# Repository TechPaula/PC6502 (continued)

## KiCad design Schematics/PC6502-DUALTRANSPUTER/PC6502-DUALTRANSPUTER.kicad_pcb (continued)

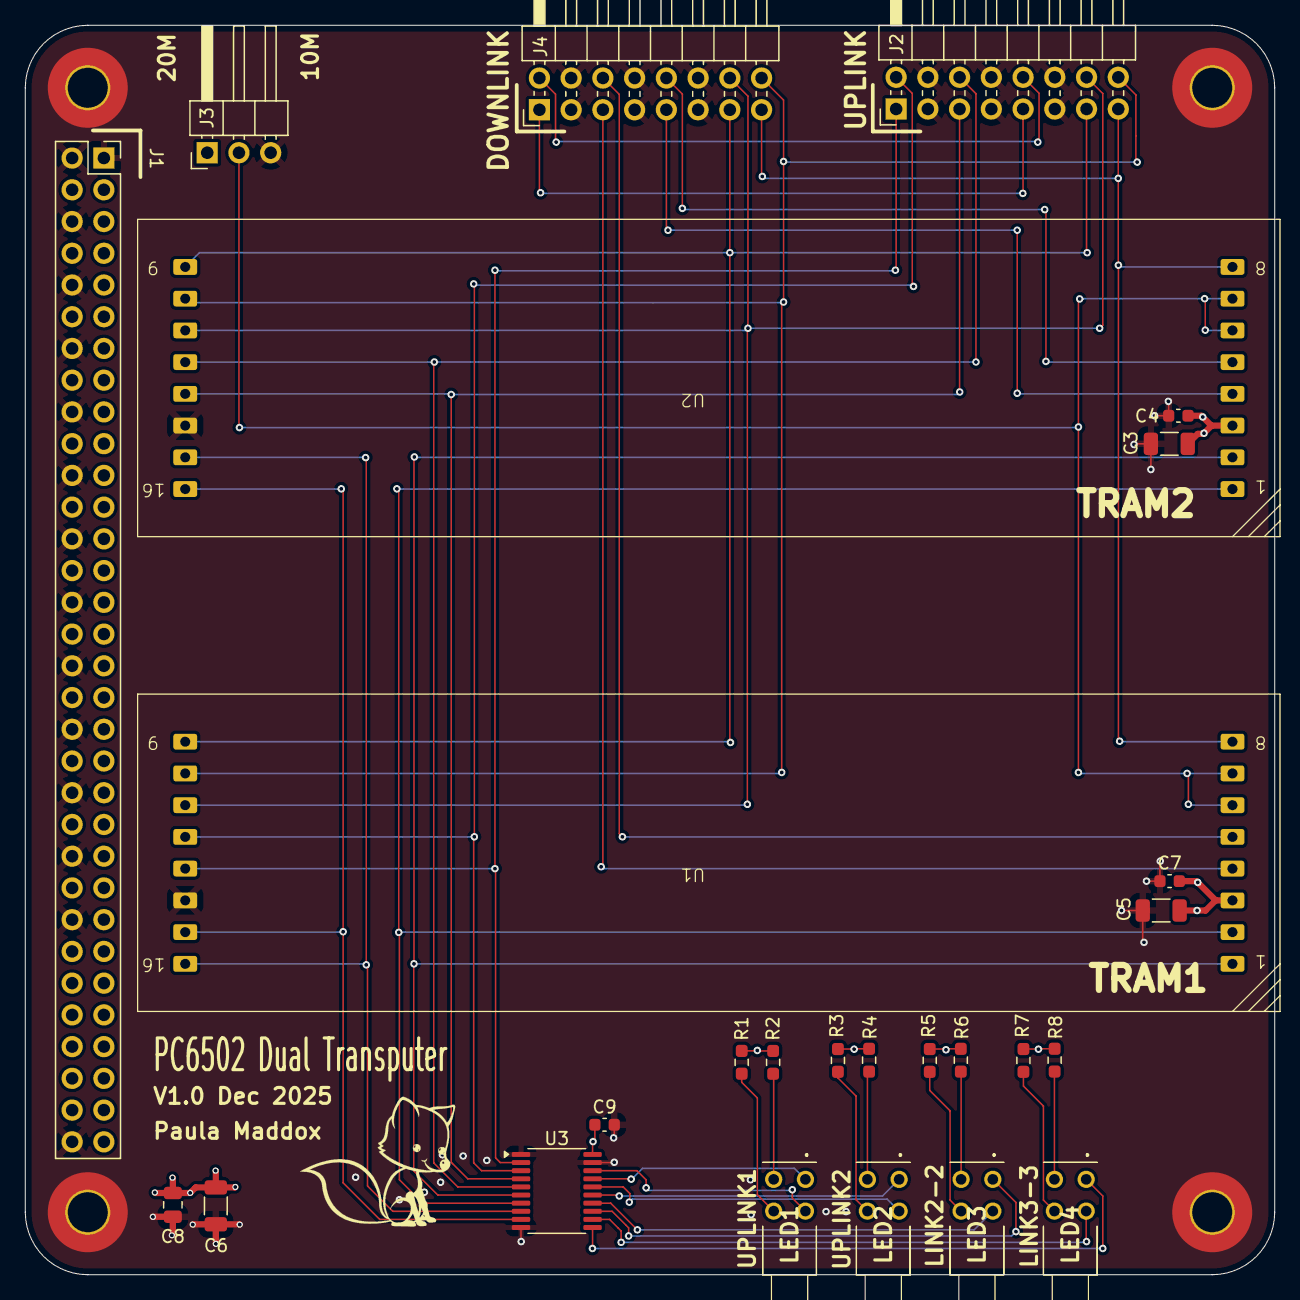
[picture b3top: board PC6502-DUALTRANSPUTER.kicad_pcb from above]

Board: 4 copper layers, 100.0 x 100.0 mm, 31 parts (0 on the bottom side), 37 nets.

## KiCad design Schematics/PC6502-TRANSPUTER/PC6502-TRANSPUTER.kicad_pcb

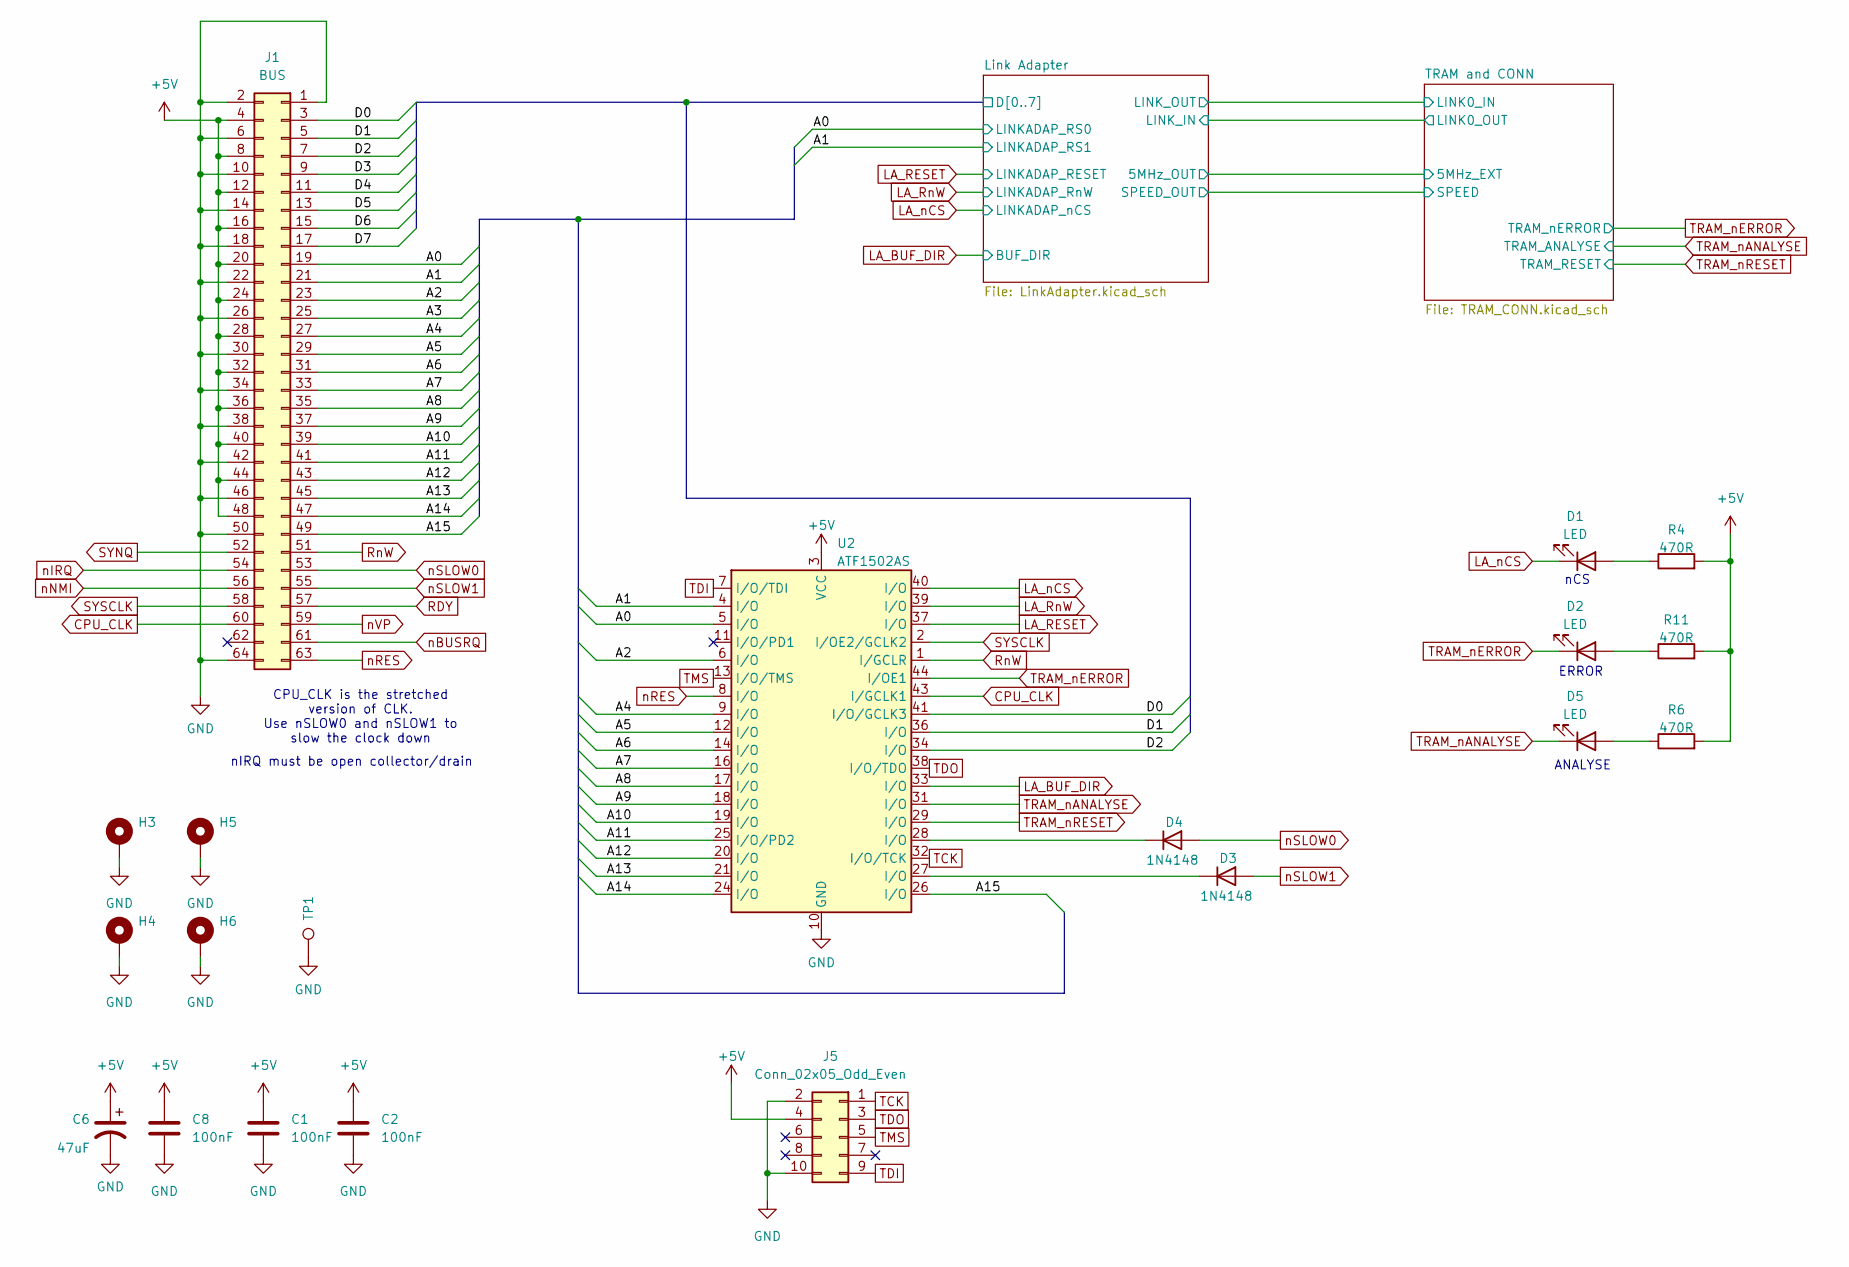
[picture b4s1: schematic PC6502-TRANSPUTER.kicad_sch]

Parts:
C1, C2: 100nF; C_0603_1608Metric
C6: 47uF; C_1206_3216Metric; LCSC C96123
C8: 100nF; C_0805_2012Metric
D1, D2, D5: LED; LTL4221NHBP; LCSC DNF
D3, D4: 1N4148; D_DO-35_SOD27_P7.62mm_Horizontal; LCSC DNF
H3, H4, H5, H6: MountingHole_Pad; MountingHole_3.2mm_M3_Pad_TopBottom; LCSC DNF
J1: BUS; PinSocket_2x32_P2.54mm_Vertical; LCSC DNF
J5: Conn_02x05_Odd_Even; PinHeader_2x05_P2.54mm_Vertical; LCSC DNF
R4, R6, R11: 470R; R_0603_1608Metric_Pad0.98x0.95mm_HandSolder; LCSC C23179
TP1: TestPoint; TestPoint_Loop_D1.80mm_Drill1.0mm_Beaded; LCSC DNF
U2: ATF1502AS; PLCC-44_THT-Socket; LCSC DNF

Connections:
+5V: C1.1, C2.1, C6.1, C8.1, J1.4, J1.8, J1.12, J1.16, J1.20, J1.24, J1.28, J1.32, J1.36, J1.40, J1.44, J1.48, J5.4, R4.2, R6.2, R11.2, U2.3 (VCC), U2.15 (VCC), U2.23 (VCC), U2.35 (VCC); also elsewhere on the board
/A0: J1.19, U2.5 (I/O); also elsewhere on the board
/A1: J1.21, U2.4 (I/O); also elsewhere on the board
/A2: J1.23, U2.6 (I/O)
/A3: J1.25
/A4: J1.27, U2.9 (I/O)
/A5: J1.29, U2.12 (I/O)
/A6: J1.31, U2.14 (I/O)
/A7: J1.33, U2.16 (I/O)
/A8: J1.35, U2.17 (I/O)
/A9: J1.37, U2.18 (I/O)
/A10: J1.39, U2.19 (I/O)
/A11: J1.41, U2.25 (I/O/PD2)
/A12: J1.43, U2.20 (I/O)
/A13: J1.45, U2.21 (I/O)
/A14: J1.47, U2.24 (I/O)
/A15: J1.49, U2.26 (I/O)
/Link Adapter/D0: J1.3, U2.41 (I/O/GCLK3); also elsewhere on the board
/Link Adapter/D1: J1.5, U2.36 (I/O); also elsewhere on the board
/Link Adapter/D2: J1.7, U2.34 (I/O); also elsewhere on the board
/Link Adapter/D3: J1.9; also elsewhere on the board
/Link Adapter/D4: J1.11; also elsewhere on the board
/Link Adapter/D5: J1.13; also elsewhere on the board
/Link Adapter/D6: J1.15; also elsewhere on the board
/Link Adapter/D7: J1.17; also elsewhere on the board
CPU_CLK: J1.60, U2.43 (I/GCLK1)
GND: C1.2, C2.2, C6.2, C8.2, H3.1, H4.1, H5.1, H6.1, J1.1, J1.2, J1.6, J1.10, J1.14, J1.18, J1.22, J1.26, J1.30, J1.34, J1.38, J1.42, J1.46, J1.50, J1.64, J5.2, J5.10, TP1.1, U2.10 (GND), U2.22 (GND), U2.30 (GND), U2.42 (GND); also elsewhere on the board
LA_BUF_DIR: U2.33 (I/O); also elsewhere on the board
LA_RESET: U2.37 (I/O); also elsewhere on the board
LA_RnW: U2.39 (I/O); also elsewhere on the board
LA_nCS: D1.1 (K), U2.40 (I/O); also elsewhere on the board
unnamed: D1.2 (A), R4.1
unnamed: D2.2 (A), R11.1
unnamed: D3.1 (K), U2.27 (I/O)
unnamed: D4.1 (K), U2.28 (I/O)
unnamed: D5.2 (A), R6.1
RDY: J1.57
RnW: J1.51, U2.1 (I/GCLR)
SYNQ: J1.52
SYSCLK: J1.58, U2.2 (I/OE2/GCLK2)
TCK: J5.1, U2.32 (I/O/TCK)
TDI: J5.9, U2.7 (I/O/TDI)
TDO: J5.3, U2.38 (I/O/TDO)
TMS: J5.5, U2.13 (I/O/TMS)
TRAM_nANALYSE: D5.1 (K), U2.31 (I/O); also elsewhere on the board
TRAM_nERROR: D2.1 (K), U2.44 (I/OE1); also elsewhere on the board
TRAM_nRESET: U2.29 (I/O); also elsewhere on the board
nBUSRQ: J1.61
nIRQ: J1.54
nNMI: J1.56
nRES: J1.63, U2.8 (I/O)
nSLOW0: D4.2 (A), J1.53
nSLOW1: D3.2 (A), J1.55
nVP: J1.59

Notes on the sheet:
ANALYSE
CPU_CLK is the stretched version of CLK. Use nSLOW0 and nSLOW1 to slow the clock down
nCS
ERROR
nIRQ must be open collector/drain

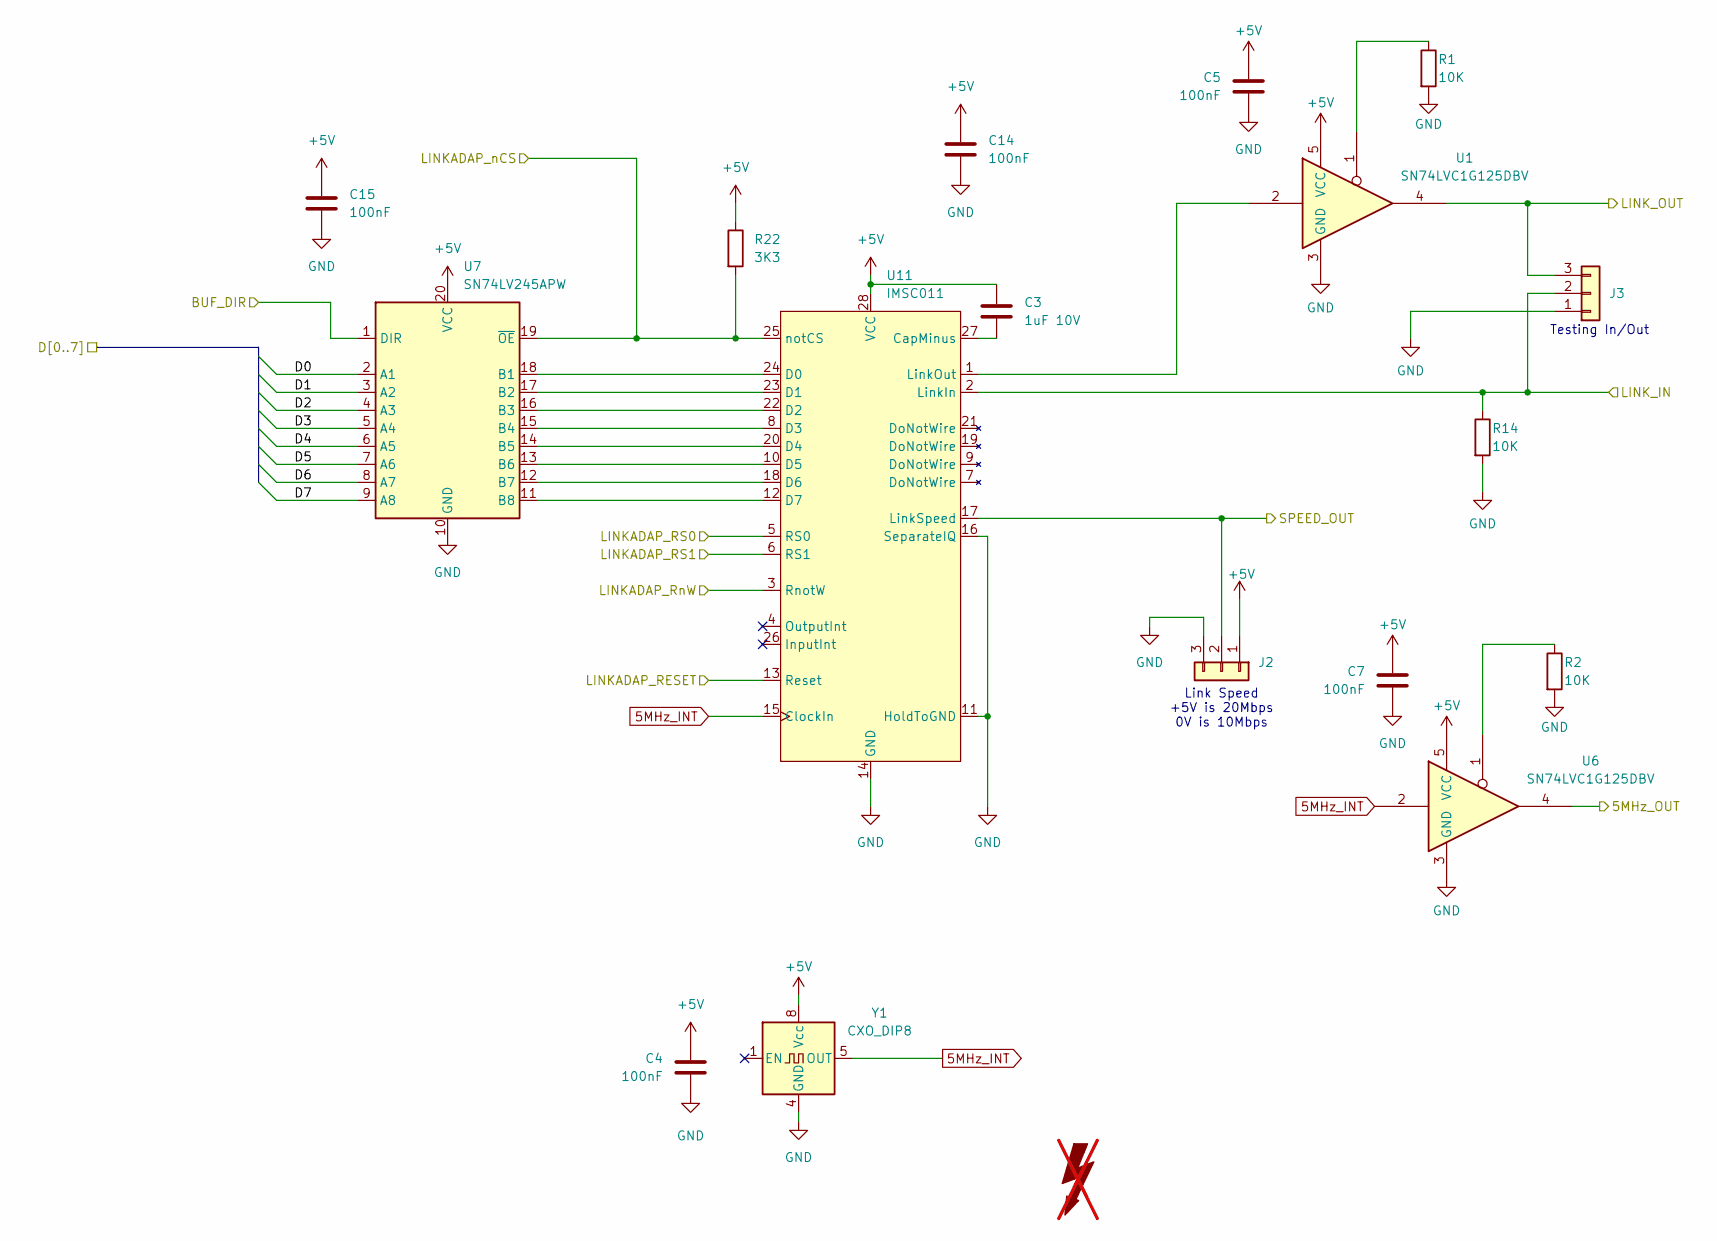
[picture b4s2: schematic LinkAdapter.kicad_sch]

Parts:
C3: 1uF 10V; C_0805_2012Metric
C4, C5, C7, C14, C15: 100nF; C_0603_1608Metric
FOX1: SYM_Flash_Large; Fox_avatar_18mm; LCSC DNF; not fitted
J2: Conn_01x03; PinHeader_1x03_P2.54mm_Horizontal
J3: Conn_01x03; PinHeader_1x03_P2.54mm_Vertical
R1, R2, R14: 10K; R_0603_1608Metric_Pad0.98x0.95mm_HandSolder; LCSC C25744
R22: 3K3; R_0603_1608Metric_Pad0.98x0.95mm_HandSolder; LCSC C25890
U1, U6: SN74LVC1G125DBV; SOT-23-5; Mouser PN 595-SN74LVC1G125DBVR
U7: SN74LV245APW; TSSOP-20_4.4x6.5mm_P0.65mm; Mouser PN 595-SN74LV245ATPWR
U11: IMSC011; DIP-28_W15.24mm
Y1: CXO_DIP8; Oscillator_DIP-8

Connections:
5MHz_INT: U6.2, U11.15 (ClockIn), Y1.5 (OUT)
+5V: C3.1, C4.1, C5.1, C7.1, C14.1, C15.1, J2.1, R22.1, U1.5 (VCC), U6.5 (VCC), U7.20 (VCC), U11.28 (VCC), Y1.8 (Vcc); also elsewhere on the board
/A0: U11.5 (RS0); also elsewhere on the board
/A1: U11.6 (RS1); also elsewhere on the board
/Link Adapter/5MHz_OUT: U6.4; also elsewhere on the board
/Link Adapter/D0: U7.2 (A1); also elsewhere on the board
/Link Adapter/D1: U7.3 (A2); also elsewhere on the board
/Link Adapter/D2: U7.4 (A3); also elsewhere on the board
/Link Adapter/D3: U7.5 (A4); also elsewhere on the board
/Link Adapter/D4: U7.6 (A5); also elsewhere on the board
/Link Adapter/D5: U7.7 (A6); also elsewhere on the board
/Link Adapter/D6: U7.8 (A7); also elsewhere on the board
/Link Adapter/D7: U7.9 (A8); also elsewhere on the board
/Link Adapter/LINK_IN: J3.2, R14.1, U11.2 (LinkIn); also elsewhere on the board
/Link Adapter/LINK_OUT: J3.3, U1.4; also elsewhere on the board
/Link Adapter/SPEED_OUT: J2.2, U11.17 (LinkSpeed); also elsewhere on the board
GND: C4.2, C5.2, C7.2, C14.2, C15.2, J2.3, J3.1, R1.2, R2.2, R14.2, U1.3 (GND), U6.3 (GND), U7.10 (GND), U11.11 (HoldToGND), U11.14 (GND), U11.16 (SeparateIQ), Y1.4 (GND); also elsewhere on the board
LA_BUF_DIR: U7.1 (DIR); also elsewhere on the board
LA_RESET: U11.13 (Reset); also elsewhere on the board
LA_RnW: U11.3 (RnotW); also elsewhere on the board
LA_nCS: R22.2, U7.19 (~OE), U11.25 (notCS); also elsewhere on the board
unnamed: R1.1, U1.1
unnamed: R2.1, U6.1
unnamed: C3.2, U11.27 (CapMinus)
unnamed: U7.18 (B1), U11.24 (D0)
unnamed: U7.17 (B2), U11.23 (D1)
unnamed: U7.16 (B3), U11.22 (D2)
unnamed: U7.15 (B4), U11.8 (D3)
unnamed: U7.14 (B5), U11.20 (D4)
unnamed: U7.13 (B6), U11.10 (D5)
unnamed: U7.12 (B7), U11.18 (D6)
unnamed: U7.11 (B8), U11.12 (D7)
unnamed: U1.2, U11.1 (LinkOut)

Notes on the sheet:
Link Speed +5V is 20Mbps 0V is 10Mbps
Testing In/Out

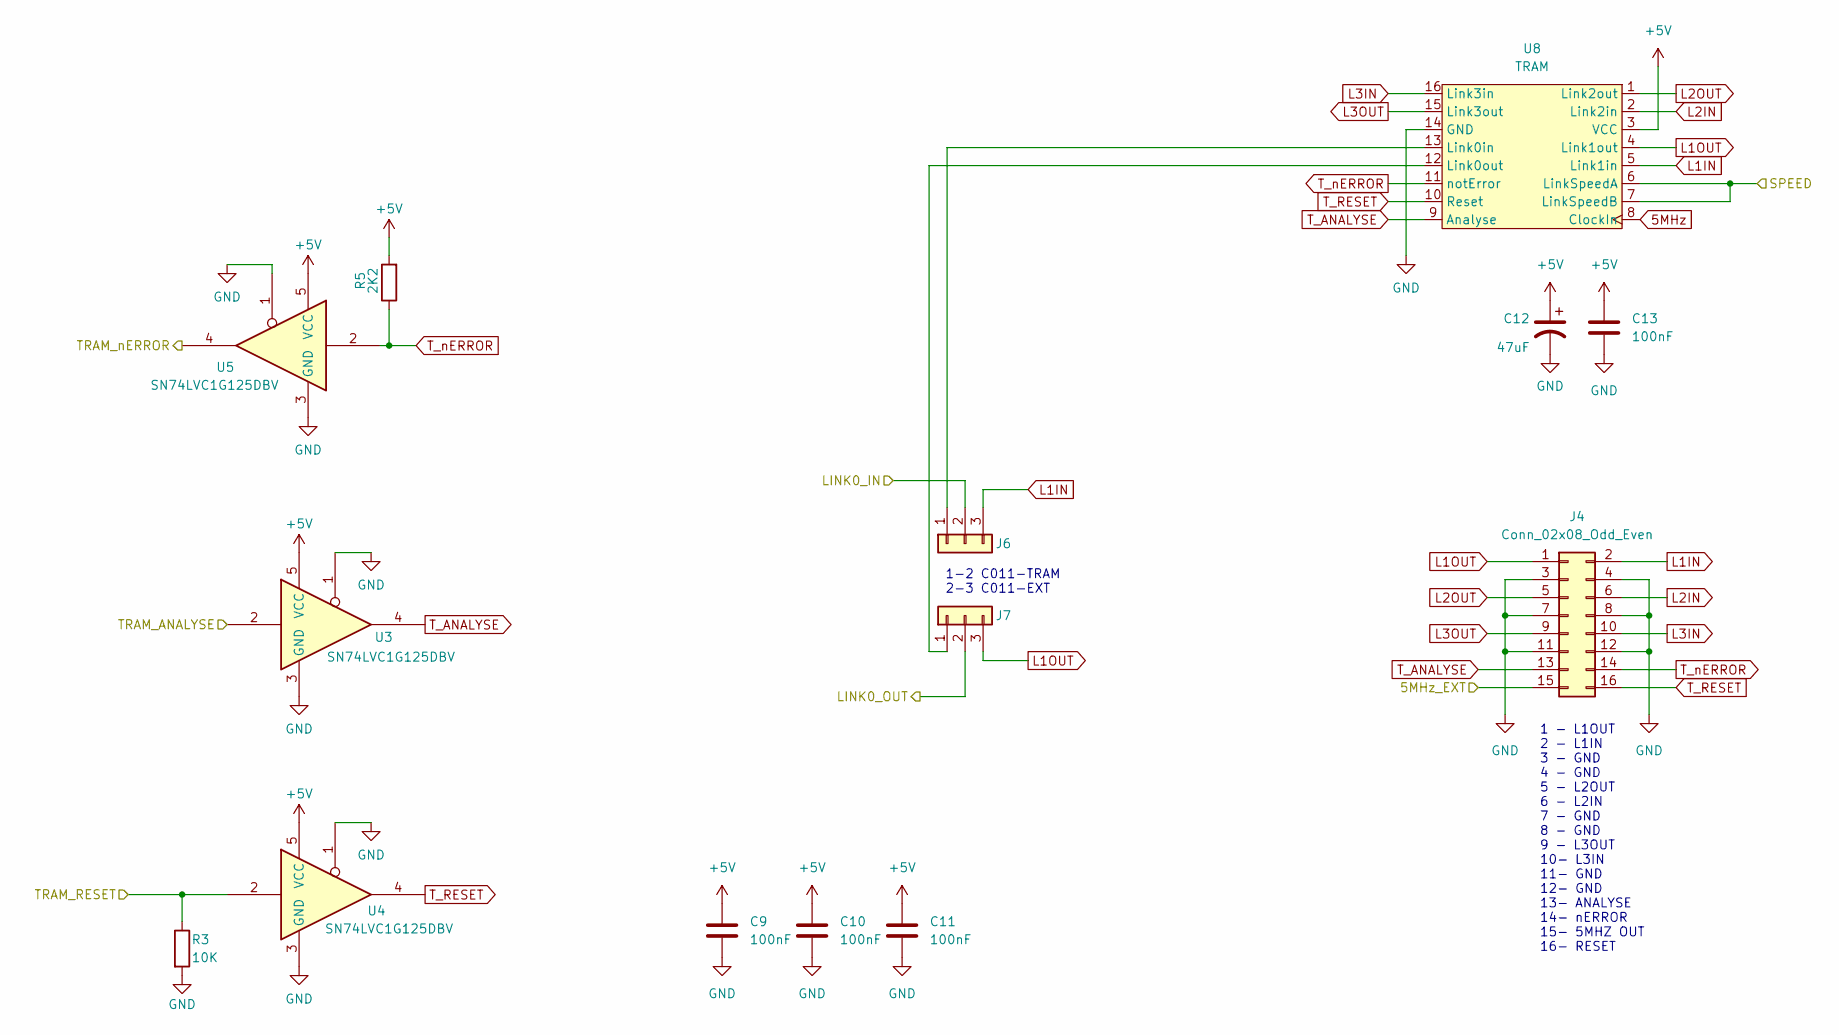
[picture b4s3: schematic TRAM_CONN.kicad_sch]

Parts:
C9, C10, C11, C13: 100nF; C_0603_1608Metric
C12: 47uF; C_1206_3216Metric; LCSC C96123
J4: Conn_02x08_Odd_Even; PinHeader_2x08_P2.54mm_Horizontal
J6, J7: Conn_01x03; PinHeader_1x03_P2.54mm_Vertical
R3: 10K; R_0603_1608Metric_Pad0.98x0.95mm_HandSolder; LCSC C25744
R5: 2K2; R_0603_1608Metric
U3, U4, U5: SN74LVC1G125DBV; SOT-23-5; Mouser PN 595-SN74LVC1G125DBVR
U8: TRAM

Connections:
5MHz: U8.8 (ClockIn)
+5V: C9.1, C10.1, C11.1, C12.1, C13.1, R5.2, U3.5 (VCC), U4.5 (VCC), U5.5 (VCC), U8.3 (VCC); also elsewhere on the board
/Link Adapter/5MHz_OUT: J4.15; also elsewhere on the board
/Link Adapter/LINK_IN: J7.2; also elsewhere on the board
/Link Adapter/LINK_OUT: J6.2; also elsewhere on the board
/Link Adapter/SPEED_OUT: U8.6 (LinkSpeedA), U8.7 (LinkSpeedB); also elsewhere on the board
GND: C9.2, C10.2, C11.2, C12.2, C13.2, J4.3, J4.4, J4.7, J4.8, J4.11, J4.12, R3.2, U3.1, U3.3 (GND), U4.1, U4.3 (GND), U5.1, U5.3 (GND), U8.14 (GND); also elsewhere on the board
L1IN: J4.2, J6.3, U8.5 (Link1in)
L1OUT: J4.1, J7.3, U8.4 (Link1out)
L2IN: J4.6, U8.2 (Link2in)
L2OUT: J4.5, U8.1 (Link2out)
L3IN: J4.10, U8.16 (Link3in)
L3OUT: J4.9, U8.15 (Link3out)
unnamed: J6.1, U8.13 (Link0in)
unnamed: J7.1, U8.12 (Link0out)
TRAM_nANALYSE: U3.2; also elsewhere on the board
TRAM_nERROR: U5.4; also elsewhere on the board
TRAM_nRESET: R3.1, U4.2; also elsewhere on the board
T_ANALYSE: J4.13, U3.4, U8.9 (Analyse)
T_RESET: J4.16, U4.4, U8.10 (Reset)
T_nERROR: J4.14, R5.1, U5.2, U8.11 (notError)

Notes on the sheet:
1 - L1OUT 2 - L1IN 3 - GND 4 - GND 5 - L2OUT 6 - L2IN 7 - GND 8 - GND 9 - L3OUT 10- L3IN 11- GND 12- GND 13- ANALYSE 14- nERROR 15- 5MHZ OUT 16- RESET
1-2 C011-TRAM 2-3 C011-EXT

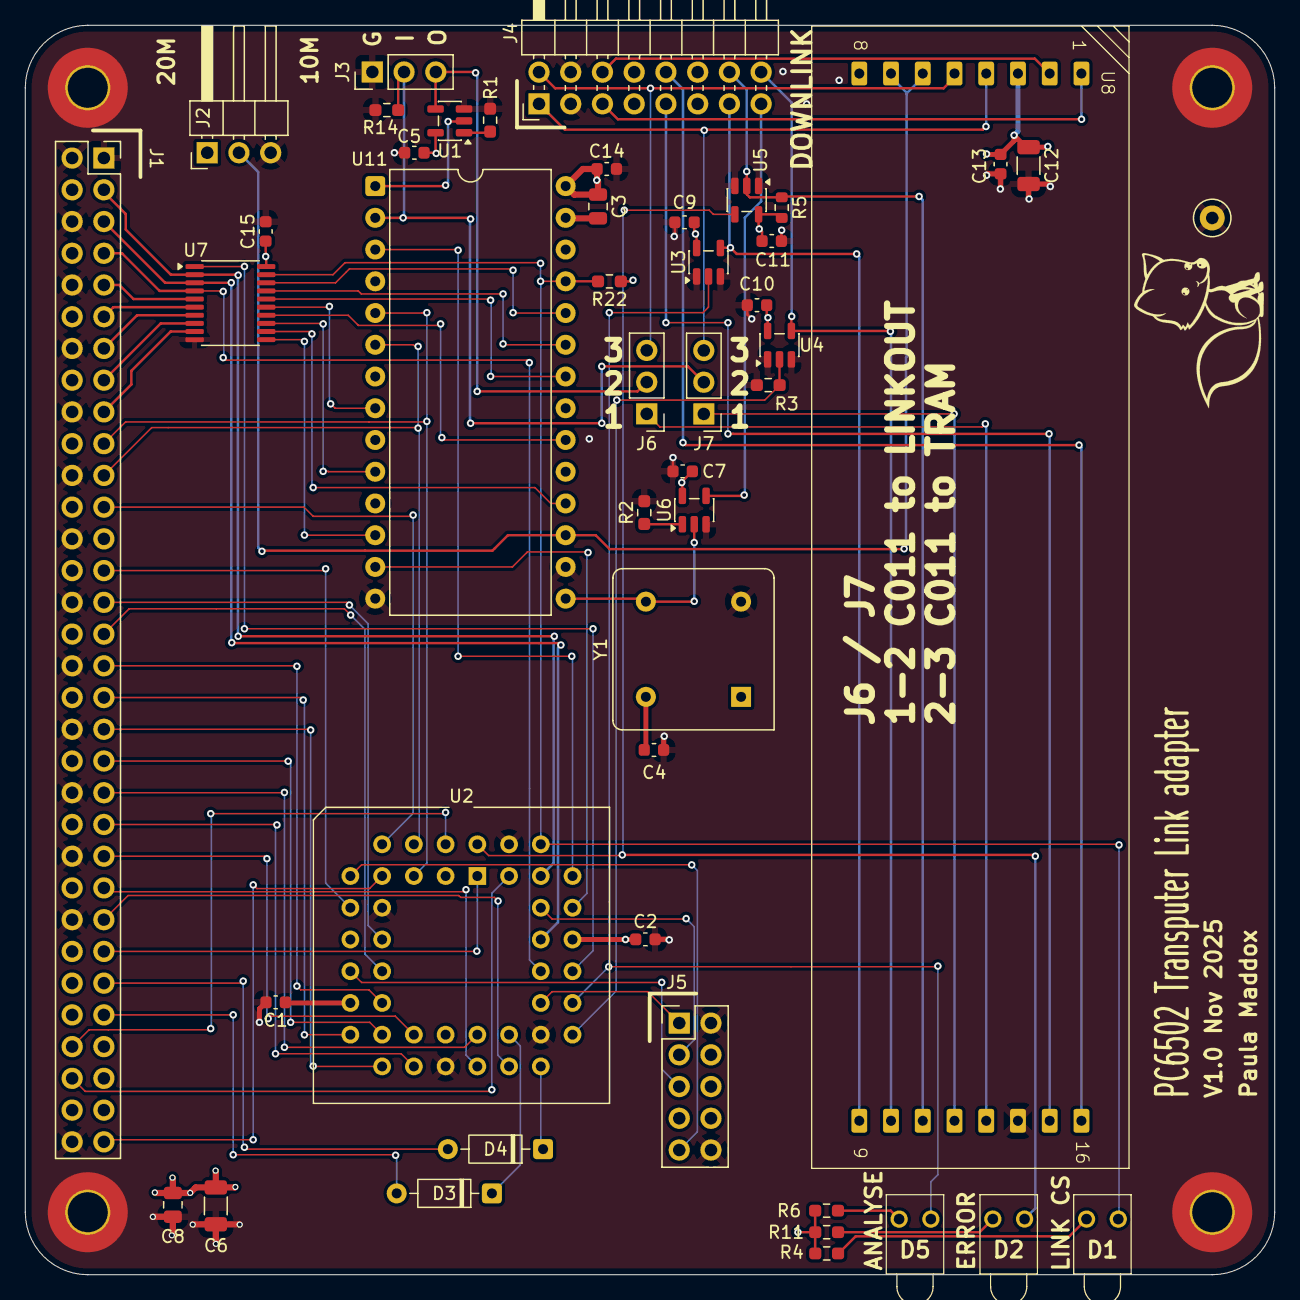
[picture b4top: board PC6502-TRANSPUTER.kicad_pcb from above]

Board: 4 copper layers, 100.0 x 100.0 mm, 52 parts (0 on the bottom side), 75 nets.

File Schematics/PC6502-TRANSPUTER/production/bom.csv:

Designator,Footprint,Quantity,Value,LCSC Part #
"C1, C10, C11, C13, C14, C15, C2, C4, C5, C7, C9",0603,11,100nF,
"C12, C6",1206,2,47uF,C96123
C3,0805,1,1uF 10V,
C8,0805,1,100nF,
"D1, D2, D5",LTL4221NHBP,3,LED,DNF
"D3, D4",D_DO-35_SOD27_P7.62mm_Horizontal,2,1N4148,DNF
"H3, H4, H5, H6",MountingHole_3.2mm_M3_Pad_TopBottom,4,MountingHole_Pad,DNF
J1,PinSocket_2x32_P2.54mm_Vertical,1,BUS,DNF
J2,PinHeader_1x03_P2.54mm_Horizontal,1,Conn_01x03,
"J3, J6, J7",PinHeader_1x03_P2.54mm_Vertical,3,Conn_01x03,
J4,PinHeader_2x08_P2.54mm_Horizontal,1,Conn_02x08_Odd_Even,
J5,PinHeader_2x05_P2.54mm_Vertical,1,Conn_02x05_Odd_Even,DNF
"R1, R14, R2, R3",0603,4,10K,C25744
"R11, R4, R6",0603,3,470R,C23179
R22,0603,1,3K3,C25890
R5,0603,1,2K2,
TP1,TestPoint_Loop_D1.80mm_Drill1.0mm_Beaded,1,TestPoint,DNF
"U1, U3, U4, U5, U6",SOT-23-5,5,SN74LVC1G125DBV,
U11,DIP-28_W15.24mm,1,IMSC011,
U2,PLCC-44_THT-Socket,1,ATF1502AS,DNF
U7,TSSOP-20_4.4x6.5mm_P0.65mm,1,SN74LVC245APW,
U8,TRAM,1,TRAM,
Y1,Oscillator_DIP-8,1,CXO_DIP8,

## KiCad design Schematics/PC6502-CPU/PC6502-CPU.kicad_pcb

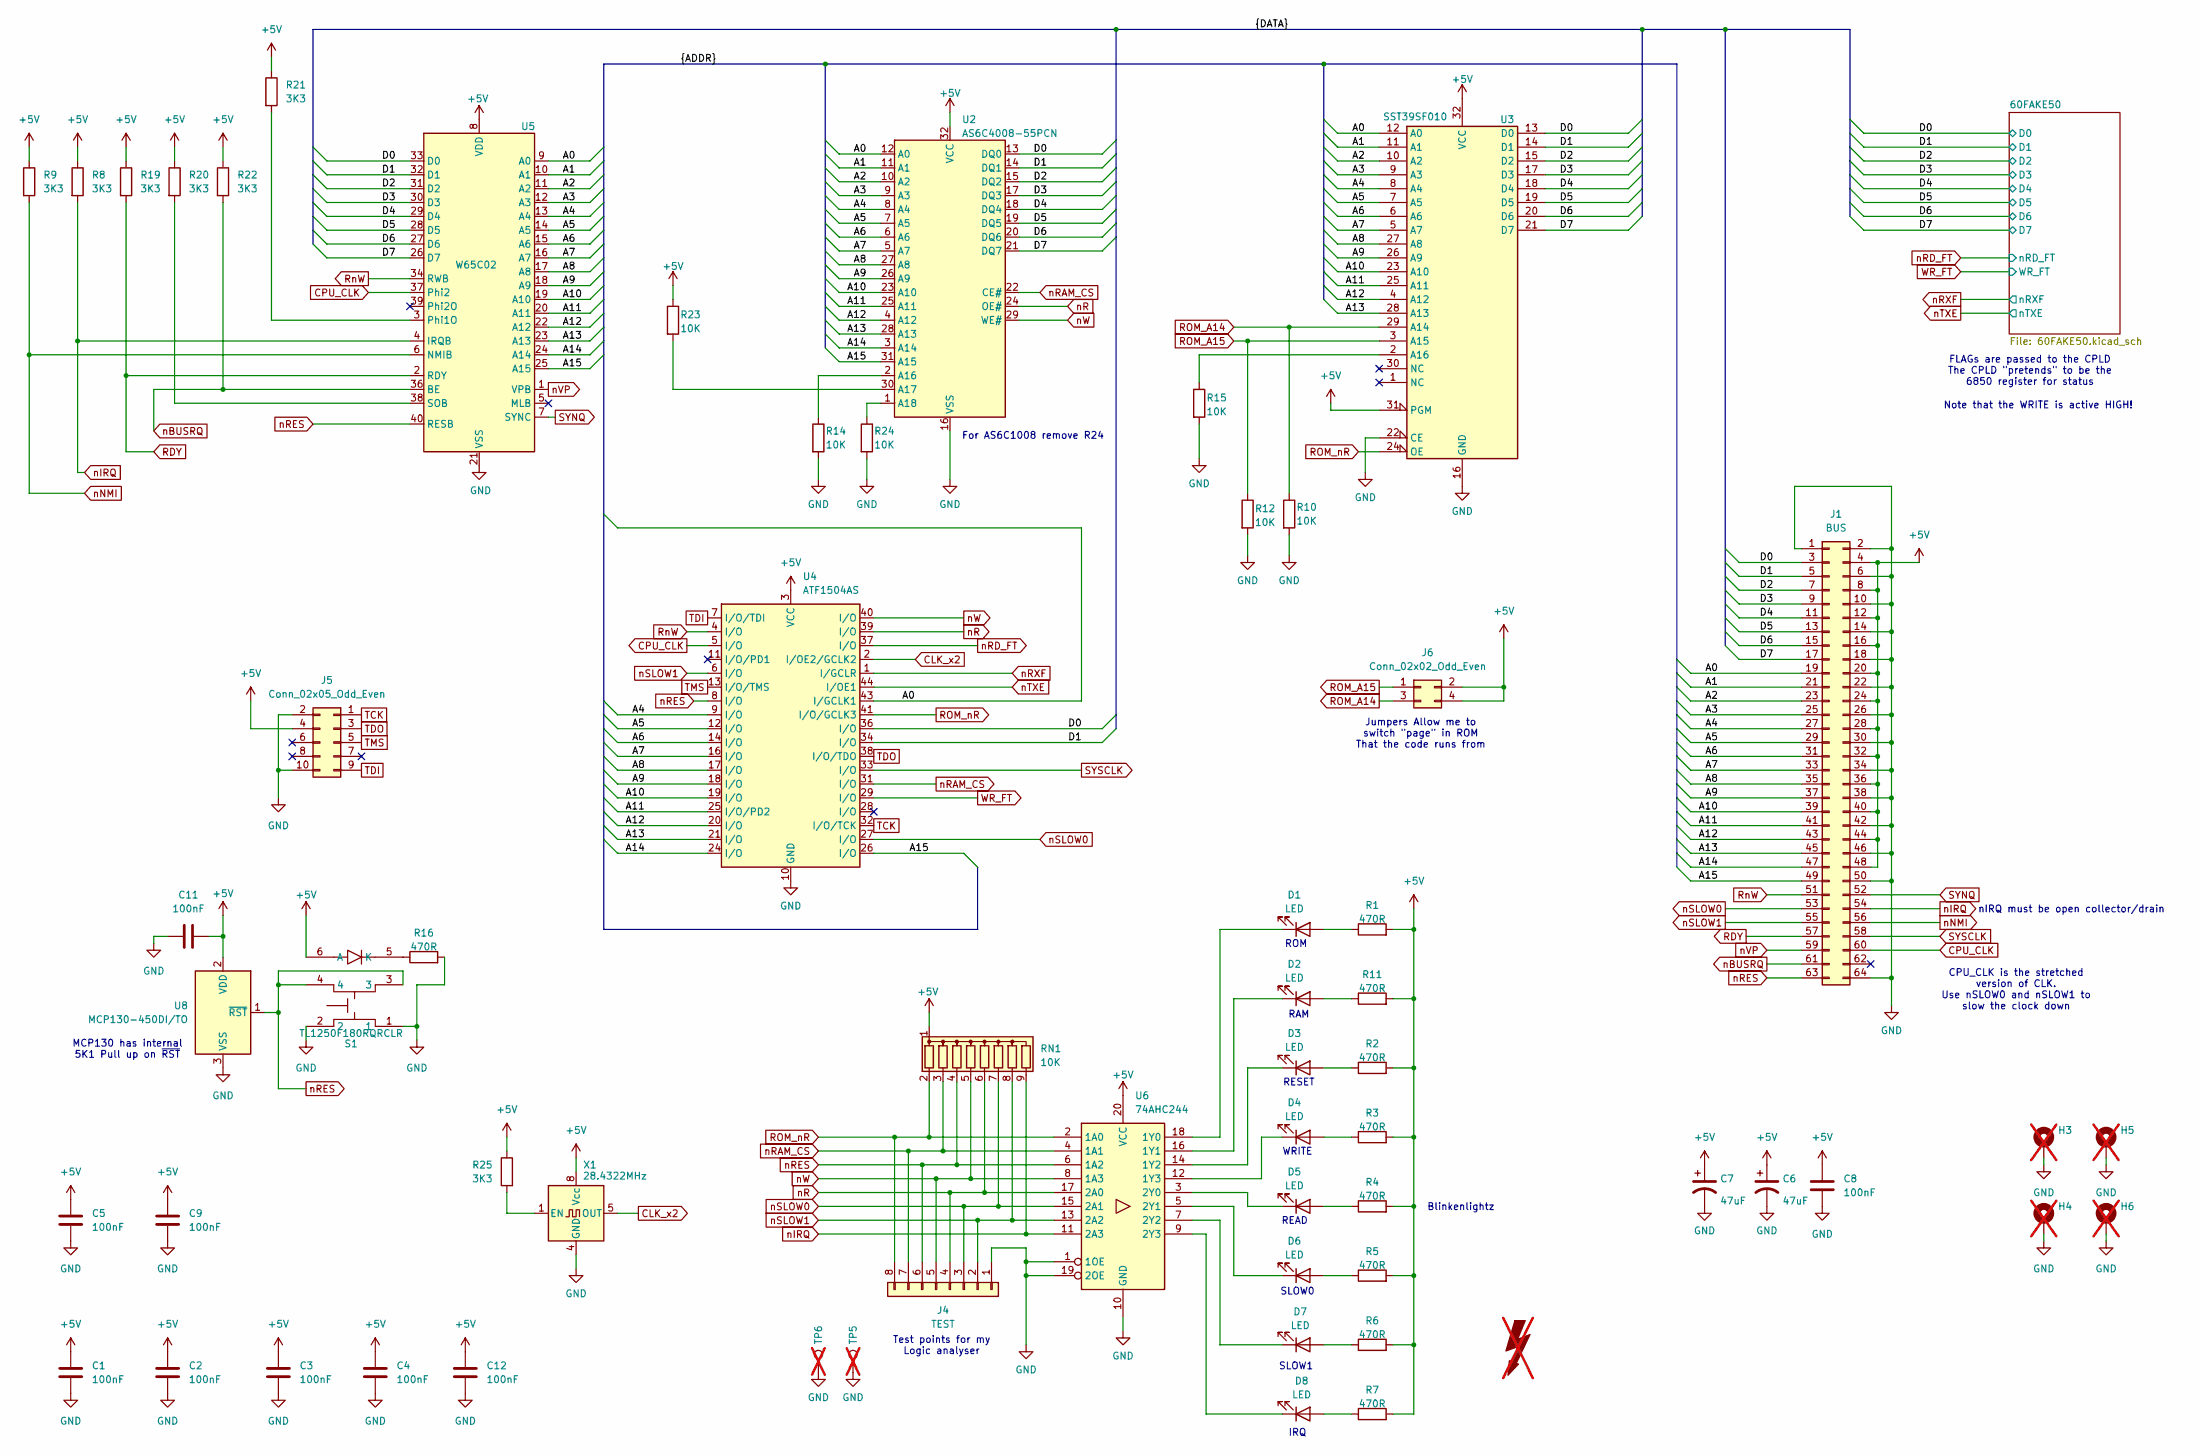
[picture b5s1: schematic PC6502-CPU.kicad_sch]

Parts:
C1, C2, C3, C4, C5, C8, C9, C11, C12: 100nF; C_0805_2012Metric; LCSC C49678
C6, C7: 47uF; C_1206_3216Metric; LCSC C96123
D1, D2, D3, D4, D5, D6, D7, D8: LED; LTL4221NHBP; LCSC DNF
FOX1: SYM_Flash_Large; Fox_avatar_18mm; LCSC DNF; not fitted
H3, H4, H5, H6: MountingHole_Pad; MountingHole_3.2mm_M3_Pad_TopBottom; LCSC DNF; not fitted
J1: BUS; PinSocket_2x32_P2.54mm_Vertical; LCSC DNF
J4: TEST; PinHeader_1x08_P2.54mm_Vertical; LCSC DNF
J5: Conn_02x05_Odd_Even; PinHeader_2x05_P2.54mm_Vertical; LCSC DNF
J6: Conn_02x02_Odd_Even; PinHeader_2x02_P2.54mm_Horizontal; LCSC D NF
R1, R2, R3, R4, R5, R6, R7, R11, R16: 470R; R_0603_1608Metric_Pad0.98x0.95mm_HandSolder; LCSC C23179
R8, R9, R19, R20, R22, R25: 3K3; R_0603_1608Metric_Pad0.98x0.95mm_HandSolder; LCSC C25890
R10, R12, R14, R15, R23, R24: 10K; R_0603_1608Metric_Pad0.98x0.95mm_HandSolder; LCSC C25744
R21: 3K3; R_0603_1608Metric_Pad0.98x0.95mm_HandSolder; LCSC DNF
RN1: 10K; R_Array_SIP9; LCSC DNF
S1: TL1250F180RQRCLR; Mouser Part Number 612-TL1250F180RQRCLR
TP5, TP6: TestPoint; TestPoint_Loop_D1.80mm_Drill1.0mm_Beaded; LCSC DNF; not fitted
U2: AS6C4008-55PCN; DIP-32_W15.24mm; LCSC DNF
U3: SST39SF010; DIP-32_W15.24mm_Socket; LCSC DNF
U4: ATF1504AS; PLCC-44_THT-Socket; LCSC DNF
U5: W65C02; DIP-40_W15.24mm_LongPads; LCSC DNF
U6: 74AHC244; DIP-20_W7.62mm_Socket; LCSC DNF
U8: MCP130-450DI/TO; TO-92_Inline; LCSC DNF
X1: 28.4322MHz; Oscillator_DIP-8; LCSC DNF

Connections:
+5V: C1.1, C2.1, C3.1, C4.1, C5.1, C6.1, C7.1, C8.1, C9.1, C11.2, C12.1, J1.4, J1.8, J1.12, J1.16, J1.20, J1.24, J1.28, J1.32, J1.36, J1.40, J1.44, J1.48, J5.4, J6.2, J6.4, R1.2, R2.2, R3.2, R4.2, R5.2, R6.2, R7.2, R8.1, R9.1, R11.2, R19.1, R20.1, R21.1, R22.1, R23.1, R25.1, RN1.1 (common), S1.6 (A), U2.32 (VCC), U3.31 (PGM), U3.32 (VCC), U4.3 (VCC), U4.15 (VCC), U4.23 (VCC), U4.35 (VCC), U5.8 (VDD), U6.20 (VCC), U8.2 (VDD), X1.8 (Vcc); also elsewhere on the board
/A0: J1.19, U2.12 (A0), U3.12 (A0), U4.43 (I/GCLK1), U5.9 (A0)
/A1: J1.21, U2.11 (A1), U3.11 (A1), U5.10 (A1)
/A2: J1.23, U2.10 (A2), U3.10 (A2), U5.11 (A2)
/A3: J1.25, U2.9 (A3), U3.9 (A3), U5.12 (A3)
/A4: J1.27, U2.8 (A4), U3.8 (A4), U4.9 (I/O), U5.13 (A4)
/A5: J1.29, U2.7 (A5), U3.7 (A5), U4.12 (I/O), U5.14 (A5)
/A6: J1.31, U2.6 (A6), U3.6 (A6), U4.14 (I/O), U5.15 (A6)
/A7: J1.33, U2.5 (A7), U3.5 (A7), U4.16 (I/O), U5.16 (A7)
/A8: J1.35, U2.27 (A8), U3.27 (A8), U4.17 (I/O), U5.17 (A8)
/A9: J1.37, U2.26 (A9), U3.26 (A9), U4.18 (I/O), U5.18 (A9)
/A10: J1.39, U2.23 (A10), U3.23 (A10), U4.19 (I/O), U5.19 (A10)
/A11: J1.41, U2.25 (A11), U3.25 (A11), U4.25 (I/O/PD2), U5.20 (A11)
/A12: J1.43, U2.4 (A12), U3.4 (A12), U4.20 (I/O), U5.22 (A12)
/A13: J1.45, U2.28 (A13), U3.28 (A13), U4.21 (I/O), U5.23 (A13)
/A14: J1.47, U2.3 (A14), U4.24 (I/O), U5.24 (A14)
/A15: J1.49, U2.31 (A15), U4.26 (I/O), U5.25 (A15)
/D0: J1.3, U2.13 (DQ0), U3.13 (D0), U4.36 (I/O), U5.33 (D0); also elsewhere on the board
/D1: J1.5, U2.14 (DQ1), U3.14 (D1), U4.34 (I/O), U5.32 (D1); also elsewhere on the board
/D2: J1.7, U2.15 (DQ2), U3.15 (D2), U5.31 (D2); also elsewhere on the board
/D3: J1.9, U2.17 (DQ3), U3.17 (D3), U5.30 (D3); also elsewhere on the board
/D4: J1.11, U2.18 (DQ4), U3.18 (D4), U5.29 (D4); also elsewhere on the board
/D5: J1.13, U2.19 (DQ5), U3.19 (D5), U5.28 (D5); also elsewhere on the board
/D6: J1.15, U2.20 (DQ6), U3.20 (D6), U5.27 (D6); also elsewhere on the board
/D7: J1.17, U2.21 (DQ7), U3.21 (D7), U5.26 (D7); also elsewhere on the board
CLK_x2: U4.2 (I/OE2/GCLK2), X1.5 (OUT)
CPU_CLK: J1.60, U4.5 (I/O), U5.37 (Phi2)
GND: C1.2, C2.2, C3.2, C4.2, C5.2, C6.2, C7.2, C8.2, C9.2, C11.1, C12.2, H3.1, H4.1, H5.1, H6.1, J1.1, J1.2, J1.6, J1.10, J1.14, J1.18, J1.22, J1.26, J1.30, J1.34, J1.38, J1.42, J1.46, J1.50, J1.64, J4.1, J5.2, J5.10, R10.2, R12.2, R14.2, R15.2, R16.2, R24.2, S1.1, S1.2, TP5.1, TP6.1, U2.16 (VSS), U3.16 (GND), U3.22 (CE), U4.10 (GND), U4.22 (GND), U4.30 (GND), U4.42 (GND), U5.21 (VSS), U6.1 (1OE), U6.10 (GND), U6.19 (2OE), U8.3 (VSS), X1.4 (GND); also elsewhere on the board
unnamed: D1.2 (A), R1.1
unnamed: D1.1 (K), U6.18 (1Y0)
unnamed: D2.2 (A), R11.1
unnamed: D2.1 (K), U6.16 (1Y1)
unnamed: D3.2 (A), R2.1
unnamed: D3.1 (K), U6.14 (1Y2)
unnamed: D4.2 (A), R3.1
unnamed: D4.1 (K), U6.12 (1Y3)
unnamed: D5.2 (A), R4.1
unnamed: D5.1 (K), U6.3 (2Y0)
unnamed: D6.2 (A), R5.1
unnamed: D6.1 (K), U6.5 (2Y1)
unnamed: D7.2 (A), R6.1
unnamed: D7.1 (K), U6.7 (2Y2)
unnamed: D8.2 (A), R7.1
unnamed: D8.1 (K), U6.9 (2Y3)
unnamed: R16.1, S1.5 (K)
unnamed: R14.1, U2.2 (A16)
unnamed: R23.2, U2.30 (A17)
unnamed: R24.1, U2.1 (A18)
unnamed: R15.1, U3.2 (A16)
unnamed: R21.2, U5.3 (Phi1O)
unnamed: R20.2, U5.38 (SOB)
unnamed: R25.2, X1.1 (EN)
RDY: J1.57, R19.2, U5.2 (RDY)
ROM_A14: J6.3, R10.1, U3.29 (A14)
ROM_A15: J6.1, R12.1, U3.3 (A15)
ROM_nR: J4.8, RN1.2 (R1), U3.24 (OE), U4.41 (I/O/GCLK3), U6.2 (1A0)
RnW: J1.51, U4.4 (I/O), U5.34 (RWB)
SYNQ: J1.52, U5.7 (SYNC)
SYSCLK: J1.58, U4.33 (I/O)
TCK: J5.1, U4.32 (I/O/TCK)
TDI: J5.9, U4.7 (I/O/TDI)
TDO: J5.3, U4.38 (I/O/TDO)
TMS: J5.5, U4.13 (I/O/TMS)
WR_FT: U4.29 (I/O); also elsewhere on the board
nBUSRQ: J1.61, R22.2, U5.36 (BE)
nIRQ: J1.54, R8.2, RN1.9 (R8), U5.4 (IRQB), U6.11 (2A3)
nNMI: J1.56, R9.2, U5.6 (NMIB)
nR: J4.4, RN1.6 (R5), U2.24 (OE#), U4.39 (I/O), U6.17 (2A0)
nRAM_CS: J4.7, RN1.3 (R2), U2.22 (CE#), U4.31 (I/O), U6.4 (1A1)
nRD_FT: U4.37 (I/O); also elsewhere on the board
nRES: J1.63, J4.6, RN1.4 (R3), S1.3, S1.4, U4.8 (I/O), U5.40 (RESB), U6.6 (1A2), U8.1 (~RST)
nRXF: U4.1 (I/GCLR); also elsewhere on the board
nSLOW0: J1.53, J4.3, RN1.7 (R6), U4.27 (I/O), U6.15 (2A1)
nSLOW1: J1.55, J4.2, RN1.8 (R7), U4.6 (I/O), U6.13 (2A2)
nTXE: U4.44 (I/OE1); also elsewhere on the board
nVP: J1.59, U5.1 (VPB)
nW: J4.5, RN1.5 (R4), U2.29 (WE#), U4.40 (I/O), U6.8 (1A3)

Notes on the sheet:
FLAGs are passed to the CPLD The CPLD "pretends" to be the 6850 register for status
Test points for my Logic analyser
Blinkenlightz
READ
MCP130 has internal 5K1 Pull up on ~{RST}
CPU_CLK is the stretched version of CLK. Use nSLOW0 and nSLOW1 to slow the clock down
SLOW1
Jumpers Allow me to switch "page" in ROM That the code runs from
WRITE
nIRQ must be open collector/drain
RAM
Note that the WRITE is active HIGH!
SLOW0
ROM
For AS6C1008 remove R24
RESET
IRQ
